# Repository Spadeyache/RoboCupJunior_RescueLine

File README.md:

/CanMV... for k230d zero development

/k230dev-yolo...enviroment to train a yolov8n model and convert to a .kmodel for k230

/teensydev... teensy4.1 developments

/xiaoesp32dev...all developments for xiao

/Electronics... all electronics development - We use EasyEDA as our main ecad software

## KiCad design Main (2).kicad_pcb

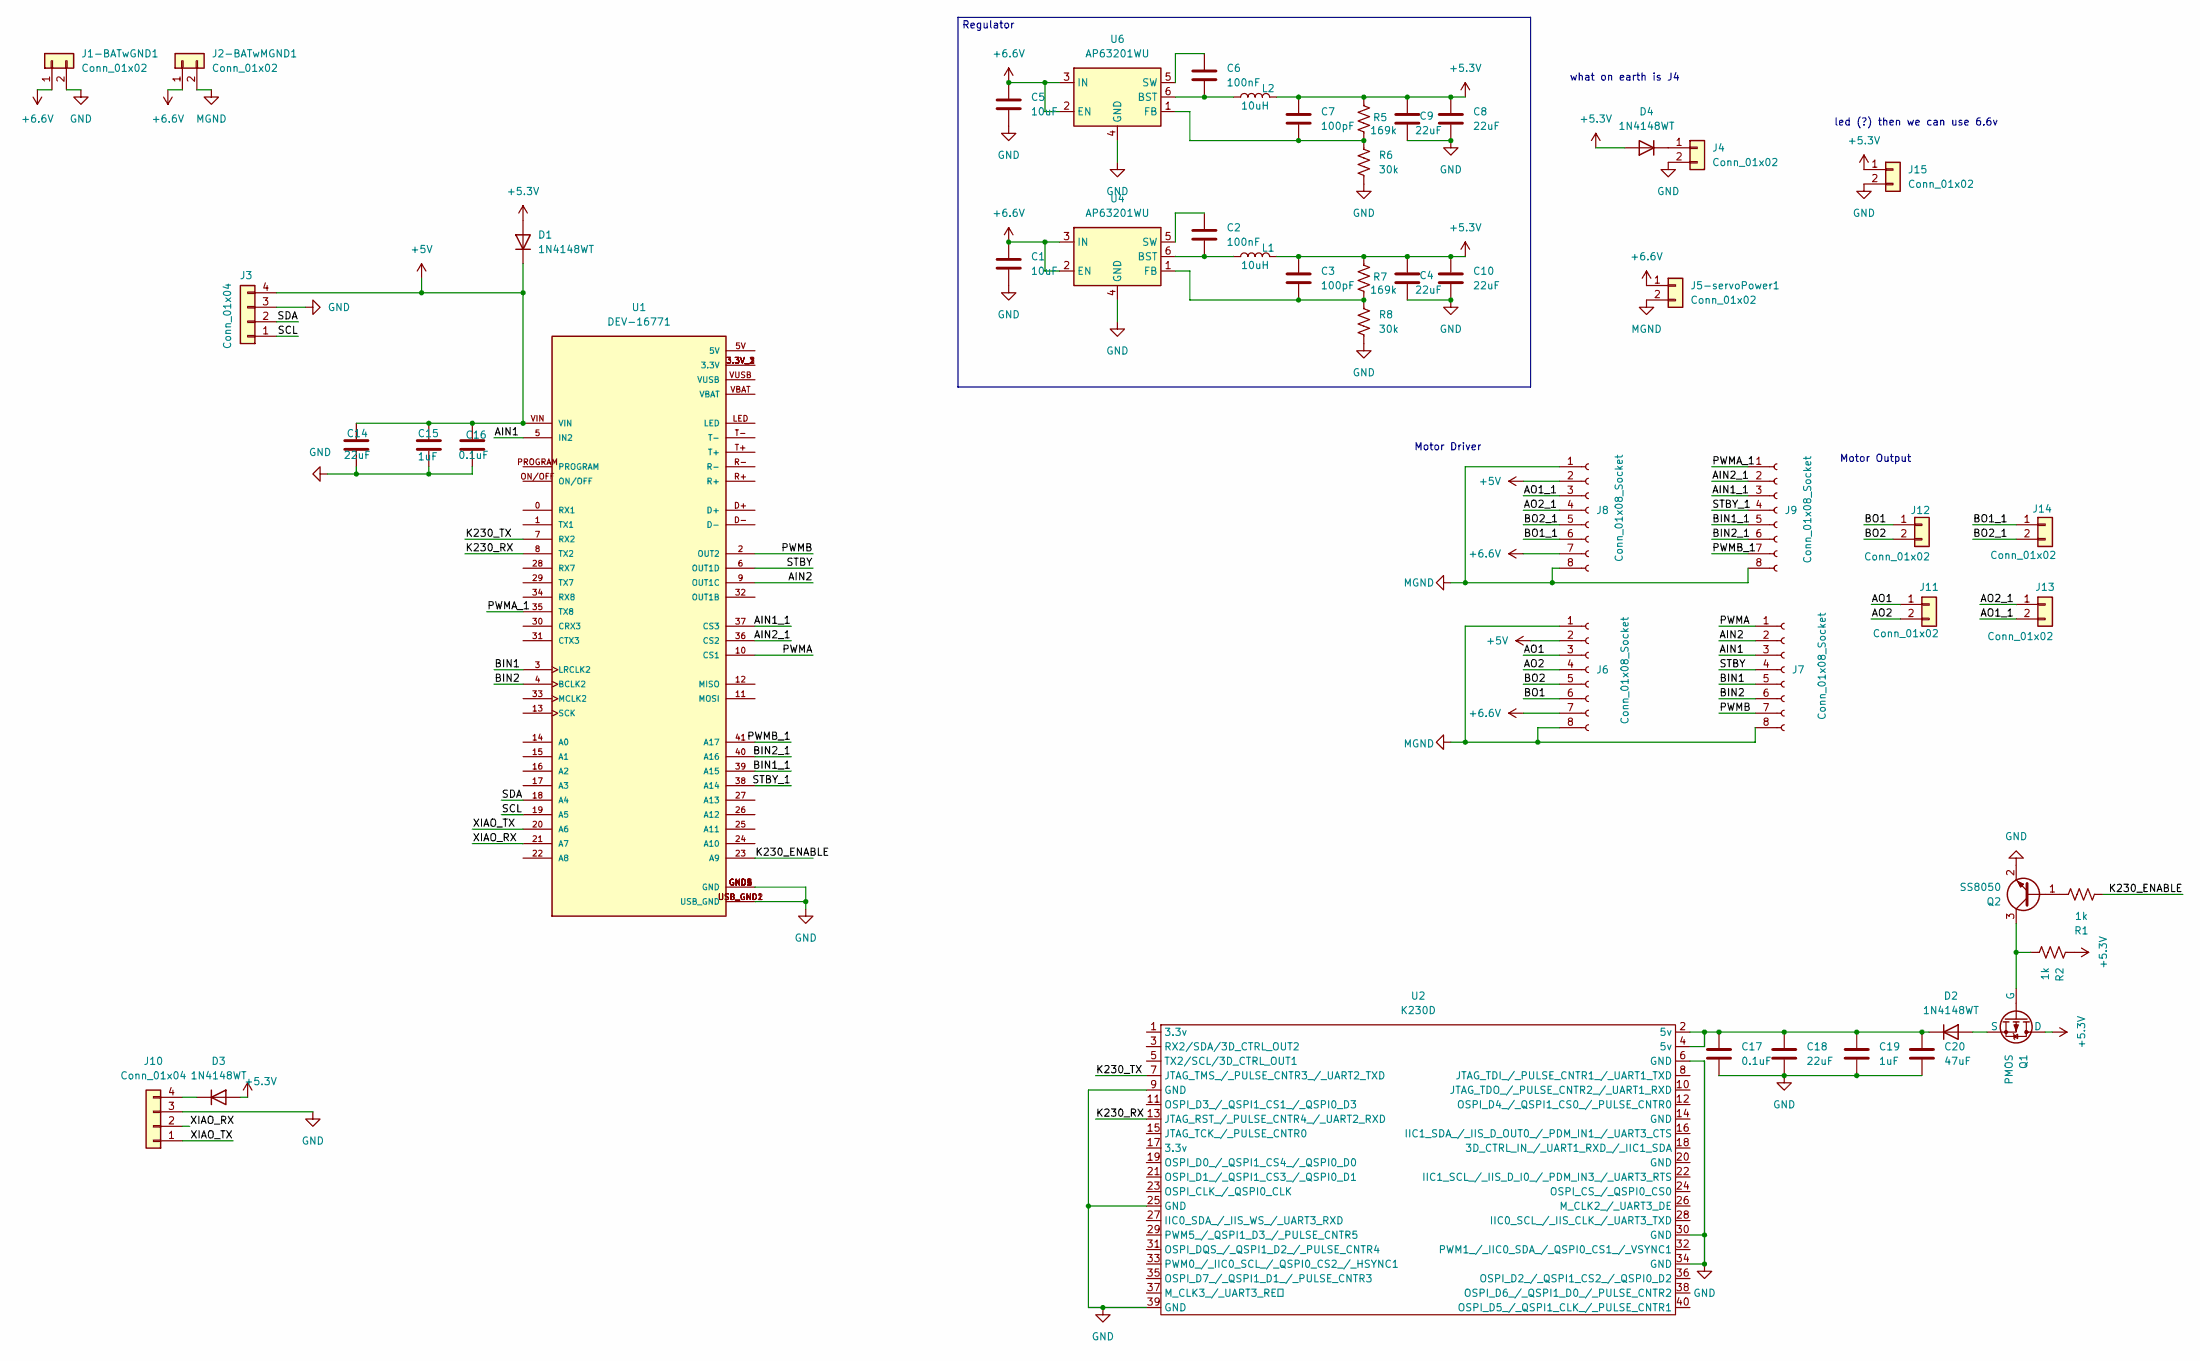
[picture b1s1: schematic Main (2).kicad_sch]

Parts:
C1, C5: 10uF; C_0603_1608Metric
C2, C6: 100nF; C_0603_1608Metric
C3, C7: 100pF; C_0603_1608Metric
C4, C8, C9, C10, C14, C18: 22uF; C_0603_1608Metric
C15, C19: 1uF; C_0603_1608Metric
C16, C17: 0.1uF; C_0603_1608Metric
C20: 47uF; C_0603_1608Metric
D1, D2, D3, D4: 1N4148WT; D_SOD-523
J1-BATwGND1, J2-BATwMGND1, J4, J5-servoPower1, J11, J12, J13, J14, J15: Conn_01x02; TE_440054-2_1x02_P2.00mm_Vertical
J3, J10: Conn_01x04; JST_XH_B4B-XH-A_1x04_P2.50mm_Vertical
J6, J7, J8, J9: Conn_01x08_Socket; PinHeader_1x08_P2.54mm_Vertical
L1, L2: 10uH; L_0603_1608Metric
Q1: PMOS; SOT-23
Q2: SS8050; SOT-23
R1, R2: 1k; R_0603_1608Metric
R5, R7: 169k; R_0603_1608Metric
R6, R8: 30k; R_0603_1608Metric
U1: DEV-16771; Teensy4.1; PARTREV 4.1
U2: K230D; PinSocket_2x20_P2.54mm_Vertical_SMD
U4, U6: AP63201WU; TSOT-23-6

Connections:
+5.3V: C3.1, C4.1, C7.1, C8.1, C9.1, C10.1, D1.2 (A), D3.2 (A), D4.2 (A), J15.1, L1.2, L2.2, Q1.1 (D), R2.1, R5.1, R7.1
+5V: C14.1, C15.1, C16.1, D1.1 (K), J3.4, J6.2, J8.2, U1.VIN
+6.6V: C1.1, C5.1, J1-BATwGND1.1, J2-BATwMGND1.1, J5-servoPower1.1, J6.7, J8.7, U4.2 (EN), U4.3 (IN), U6.2 (EN), U6.3 (IN)
/AIN1: J7.3, U1.5 (IN2)
/AIN1_1: J9.3, U1.37 (CS3)
/AIN2: J7.2, U1.9 (OUT1C)
/AIN2_1: J9.2, U1.36 (CS2)
/AO1: J6.3, J11.1
/AO1_1: J8.3, J13.2
/AO2: J6.4, J11.2
/AO2_1: J8.4, J13.1
/BIN1: J7.5, U1.3 (LRCLK2)
/BIN1_1: J9.5, U1.39 (A15)
/BIN2: J7.6, U1.4 (BCLK2)
/BIN2_1: J9.6, U1.40 (A16)
/BO1: J6.6, J12.1
/BO1_1: J8.6, J14.1
/BO2: J6.5, J12.2
/BO2_1: J8.5, J14.2
/K230_ENABLE: R1.1, U1.23 (A9)
/K230_RX: U1.8 (TX2), U2.13 (JTAG_RST_/_PULSE_CNTR4_/_UART2_RXD)
/K230_TX: U1.7 (RX2), U2.7 (JTAG_TMS_/_PULSE_CNTR3_/_UART2_TXD)
/PWMA: J7.1, U1.10 (CS1)
/PWMA_1: J9.1, U1.35 (TX8)
/PWMB: J7.7, U1.2 (OUT2)
/PWMB_1: J9.7, U1.41 (A17)
/SCL: J3.1, U1.19 (A5)
/SDA: J3.2, U1.18 (A4)
/STBY: J7.4, U1.6 (OUT1D)
/STBY_1: J9.4, U1.38 (A14)
/XIAO_RX: J10.2, U1.21 (A7)
/XIAO_TX: J10.1, U1.20 (A6)
GND: C1.2, C4.2, C5.2, C8.2, C9.2, C10.2, C14.2, C15.2, C16.2, C17.2, C18.2, C19.2, C20.2, J1-BATwGND1.2, J3.3, J4.2, J10.3, J15.2, Q2.2 (E), R6.2, R8.2, U1.GND1 (GND), U1.GND2 (GND), U1.GND3 (GND), U1.GND4 (GND), U1.GND5 (GND), U1.USB_GND1 (USB_GND), U1.USB_GND2 (USB_GND), U2.6 (GND), U2.9 (GND), U2.25 (GND), U2.30 (GND), U2.34 (GND), U2.39 (GND), U4.4 (GND), U6.4 (GND)
MGND: J2-BATwMGND1.2, J5-servoPower1.2, J6.1, J6.8, J7.8, J8.1, J8.8, J9.8
unnamed: D2.2 (A), Q1.3 (S)
unnamed: C17.1, C18.1, C19.1, C20.1, D2.1 (K), U2.2 (5v), U2.4 (5v)
unnamed: D3.1 (K), J10.4
unnamed: D4.1 (K), J4.1
unnamed: Q1.2 (G), Q2.3 (C), R2.2
unnamed: Q2.1 (B), R1.2
unnamed: U1.3.3V_1 (3.3V), U1.3.3V_2 (3.3V), U1.3.3V_3 (3.3V)
unnamed: C2.2, L1.1, U4.6 (BST)
unnamed: C3.2, R7.2, R8.1, U4.1 (FB)
unnamed: C2.1, U4.5 (SW)
unnamed: C6.2, L2.1, U6.6 (BST)
unnamed: C7.2, R5.2, R6.1, U6.1 (FB)
unnamed: C6.1, U6.5 (SW)

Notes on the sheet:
Regulator
led (?) then we can use 6.6v
Motor Output
what on earth is J4
Motor Driver

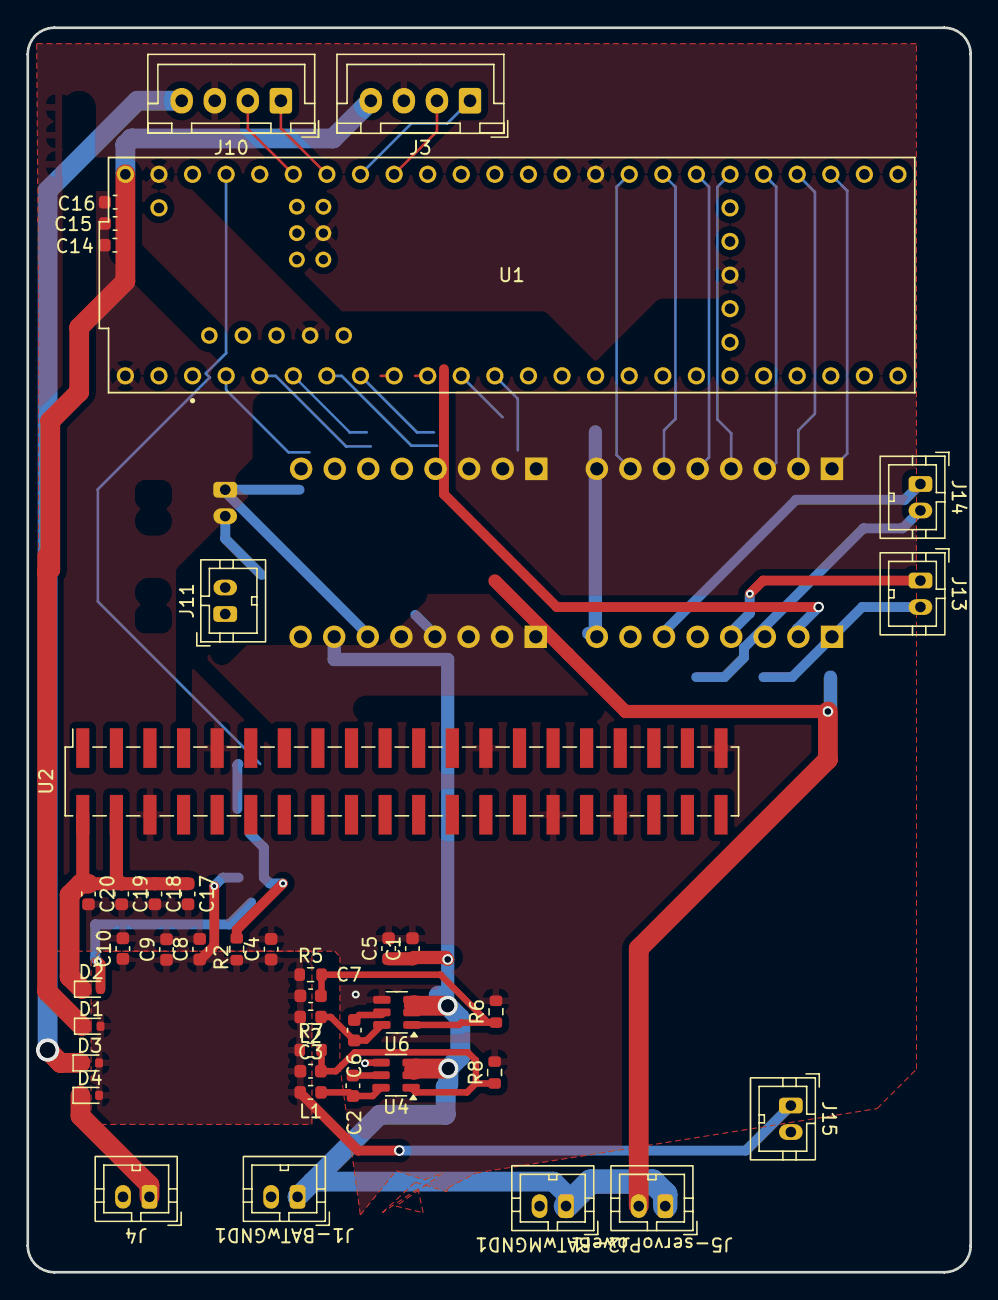
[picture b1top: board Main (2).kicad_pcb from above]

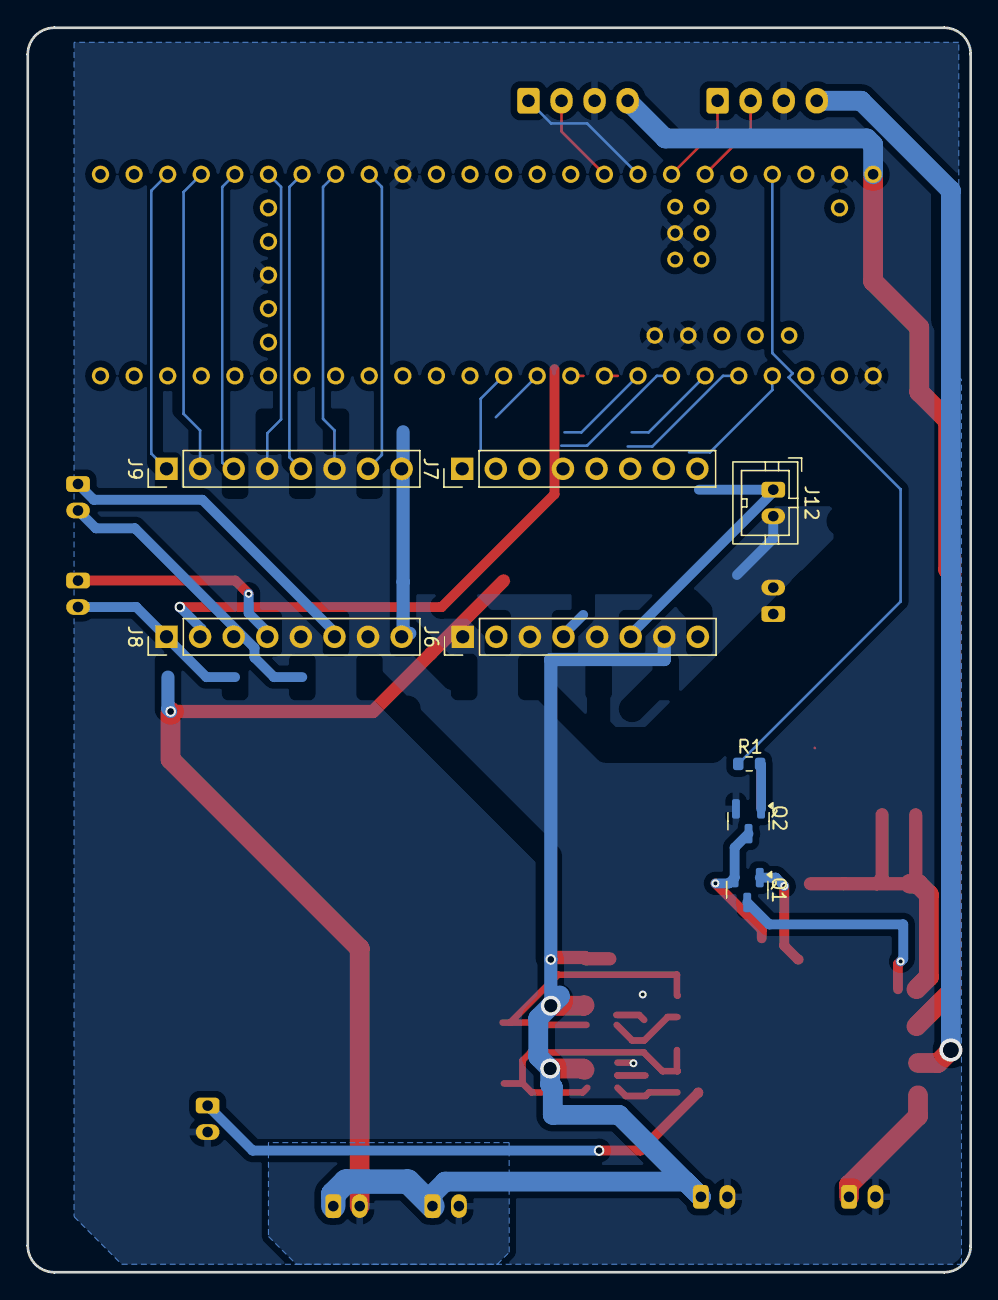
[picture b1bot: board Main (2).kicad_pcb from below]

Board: 2 copper layers, 71.3 x 94.1 mm, 50 parts (8 on the bottom side), 47 nets.

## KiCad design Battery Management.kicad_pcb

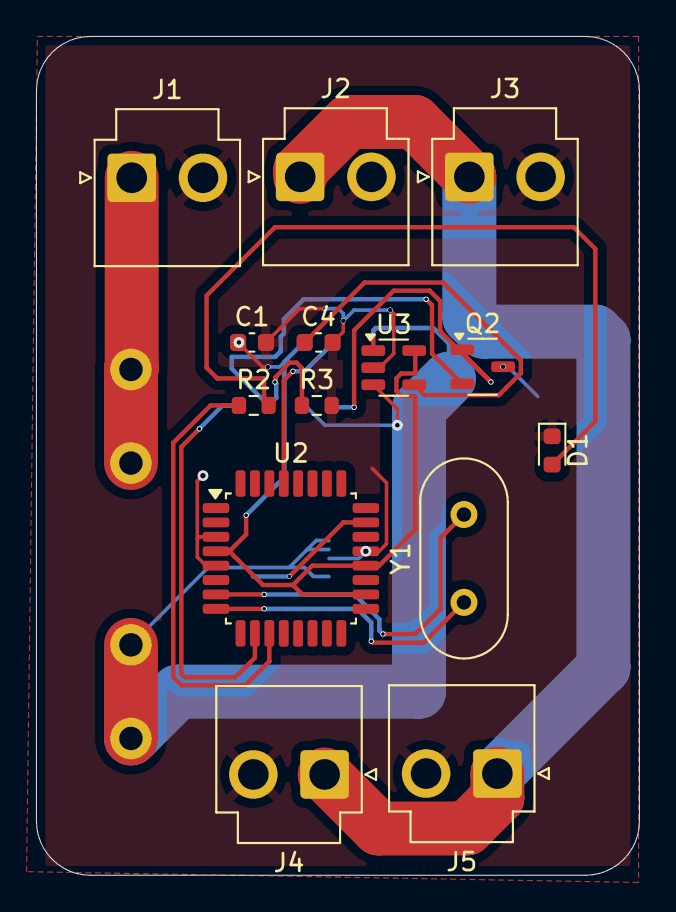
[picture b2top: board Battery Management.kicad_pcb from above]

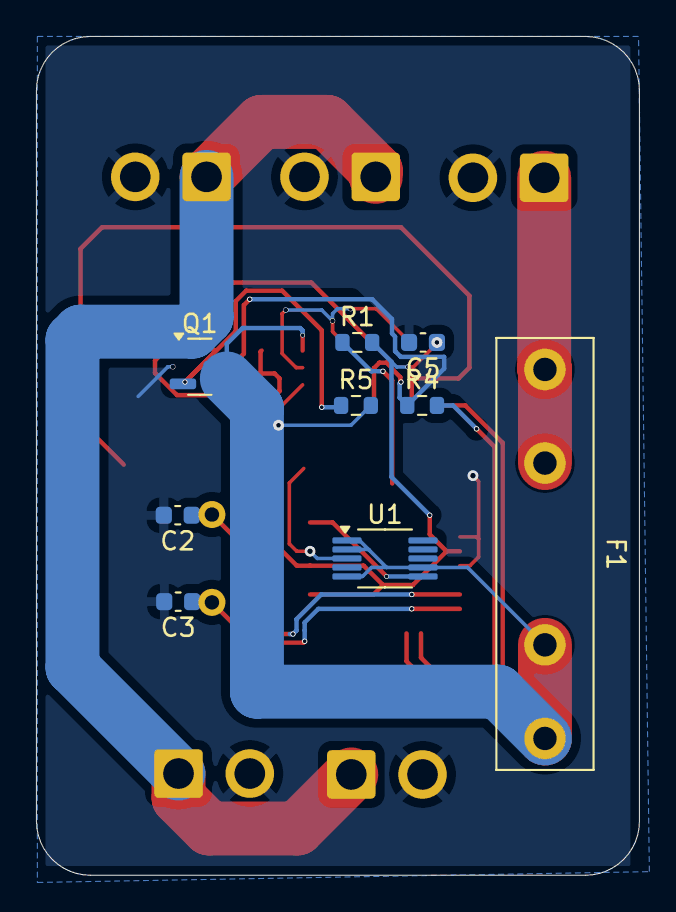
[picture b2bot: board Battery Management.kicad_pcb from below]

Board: 2 copper layers, 33.5 x 46.6 mm, 23 parts (9 on the bottom side), 15 nets.

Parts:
C1: 0.1uF; C_0603_1608Metric
C2, C3: 22pF; C_0603_1608Metric
C4: 470pF; C_0603_1608Metric
C5: 2.2uF; C_0603_1608Metric
D1: LED; D_0603_1608Metric
F1: Fuse; Fuseholder_Littelfuse_445_030_series_5x20mm
J1, J2, J3, J4, J5: Conn_01x02; JST_VH_B2P-VH-B_1x02_P3.96mm_Vertical
Q1: PMOS; SOT-23
Q2: NMOS; SOT-23-3
R1, R2, R3, R5: 10K; R_0603_1608Metric
R4: 100; R_0603_1608Metric
U1: LT1996CMS_PBF; MSOP-10_3x3mm_P0.5mm
U2: ATmega328P-A; TQFP-32_7x7mm_P0.8mm
U3: MIC5219-5.0YM5; SOT-23-5
Y1: Crystal; Crystal_HC49-U_Vertical

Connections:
+5V: C1.1, C5.1, R1.2, U2.4 (VCC), U2.6 (VCC), U2.18 (AVCC), U2.20 (AREF), U3.5 (OUT)
+6.6V: J2.1, J3.1, J4.1, J5.1, Q1.1 (D)
+BATT: F1.2, Q1.3 (S), R5.2, U1.1 (P9), U1.2 (P27), U1.5 (REF), U1.7 (VCC), U3.1 (IN), U3.3 (EN)
GND: C1.2, C2.2, C3.2, C4.2, C5.2, D1.1 (K), J1.2, J2.2, J3.2, J4.2, J5.2, Q2.3 (S), R3.2, U1.3 (P81), U1.4 (VEE), U2.3 (GND), U2.5 (GND), U2.21 (GND), U3.2 (GND)
unnamed: D1.2 (A), R2.2
unnamed: F1.1, J1.1
unnamed: Q1.2 (G), Q2.1 (D), R5.1
unnamed: Q2.2 (G), R3.1, R4.1
unnamed: R4.2, U2.10 (PD6)
unnamed: R2.1, U2.11 (PD7)
unnamed: C2.1, U2.7 (XTAL1/PB6), Y1.2
unnamed: C3.1, U2.8 (XTAL2/PB7), Y1.1
unnamed: R1.1, U2.29 (~RESET/PC6)
unnamed: C4.1, U3.4 (BP)
VREF: U1.6 (OUT), U2.23 (PC0)

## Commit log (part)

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2025-06-28 initial commit: communication of VL53L1X
2025-06-28 added a fix to the basic libraly, reading the distance
2025-06-28 switched the order of code so degub is easier
2025-06-28 added I2C ID change for left ToF. Have not tested with Right ToF yet(dont have 2 sensors)
2025-07-05 added the ploter code
2025-07-05 added Sparkfun ToF lib
2025-07-05 updated the readme in yacheVL53L1X
2025-08-30 add gitignore
2025-08-30 ignore
2025-08-30 Fix gitignore: untrack and properly ignore KiCad cache files
2025-08-30 settingup
2025-10-29 Add files via upload
    New battery files
2025-10-30 Add files via upload
    Main
2025-10-31 Add files via upload
    Done, forgive the trace lengths or I die
2025-11-06 Add files via upload
    I uploaded wrong versions I just saw
2025-12-22 Add files via upload
    Please help make smaller!
2025-12-26 Add files via upload
    Power set contains motor connections and rectifiers. Logic set is the rest.
2025-12-26 folder organnized
2026-01-02 powermanagmen
2026-01-06 Add files via upload
    Bro ong EasyEda did not let me download the activation file!
2026-01-06 powermanagmen merged all circuit
2026-01-07 kicad update
2026-01-10 overwrite to match local
2026-01-10 created dev folders for each board
2026-01-12 yolo
2026-01-12 yolotest
2026-01-12 moded to can
2026-01-14 powerman
2026-01-24 imu code
2026-01-24 xiao board update
2026-01-28 pcbdesign
2026-01-28 updated pcb
2026-01-29 teensy pcb design
2026-01-29 k230&pow schema update
2026-01-30 debuglog
2026-01-30 k230 board design
2026-01-31 power and k230 fix
2026-01-31 pow done
2026-01-31 logo k230
2026-02-02 Add files via upload
    Updated
2026-02-25 teensydev
2026-02-25 imubaseSTScontroll and printQUAT was added to yacheMPU
2026-02-26 teensydev sts and mpu code optimization
2026-02-27 further optimization of sts and imu controll
2026-02-28 added code to test the onnx model in pc
2026-03-01 binary read teensycode
2026-03-01 rename for convention
2026-03-01 k230uart
2026-03-08 Electronocs Teensy and power pcb update
2026-03-09 electronics update
2026-03-14 canmv
2026-03-14 update filenames
2026-03-14 k230model dev
2026-03-15 xiao ccamera libraries
2026-03-15 xiao on/off controol
2026-03-16 serial camera image
2026-03-17 yolotrained and xiao serial dev
2026-03-17 grayscale is done. hsv convertion without wbmodel calibratio with wb model calibration and optimization for running in main code it to be implemented
2026-03-17 updte my todo
2026-03-17 clean up xiao printRawGrayHSV
2026-03-18 xiao clean up, calibration
2026-03-18 everything but calibration is tested
2026-03-18 xiao camera and uart
2026-03-18 pid update
2026-03-18 add line edge case identification
2026-03-19 tested XIAO : PID and color detec color detection logic working
2026-03-21 teensy update
2026-03-29 yolotrain3
2026-03-29 kmodel convertion with nncase 2.9.0 verified on k230d
2026-03-29 update 3-29
2026-03-29 gitignore update
2026-03-29 Apply .gitignore changes
2026-03-29 files renamed in Electronics
2026-04-04 krs3301 and hs45hb parallel operation
2026-04-04 serial xiao
2026-04-04 pid verified
2026-04-06 2 sensor pid
2026-04-06 PID with center of mass
2026-04-07 reactive pid
2026-04-10 new camera tested
2026-04-13 xiao and teensy working tgt
2026-04-14 verified PD
2026-04-17 xiao pid improvment
2026-04-17 setup optimization
2026-04-17 xiao camera FOV changed and upbers adjusted - exeptional preformance
2026-04-17 row30 PID flawless
2026-04-18 line code is done
2026-04-21 line follow perfection
2026-04-24 nonblocking StateMachine Implementation
2026-04-26 intersection and evac updates
2026-04-26 k230 uart implemented
2026-04-27 mapping and DMP imu
2026-05-04 remap files
2026-05-05 camera identification upgrade
2026-05-06 teensy selectes xiao mode
2026-05-06 starting xiao clean up
2026-05-07 xiao mode selection from teensy
